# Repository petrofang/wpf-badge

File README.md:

# wpf-badge
A Printed Circuit Board design for When Pigs Fly, 
inspired by original artwork of Mark Poulin.

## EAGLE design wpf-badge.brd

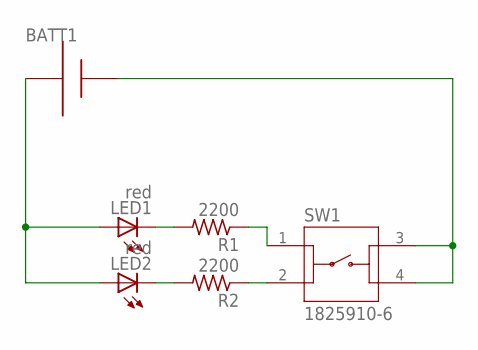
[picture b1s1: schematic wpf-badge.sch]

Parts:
BATT1: AAA; 12BH412
LED1, LED2: red; LED3MM
R1, R2: 2200; 0204/7
SW1: 1825910-6; SW_1825910-6-4

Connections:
unnamed: LED2.K (C), R2.2
unnamed: LED1.K (C), R1.2
unnamed: BATT1.+, SW1.3, SW1.4
unnamed: R1.1, SW1.1
unnamed: R2.1, SW1.2
unnamed: BATT1.-, LED1.A, LED2.A

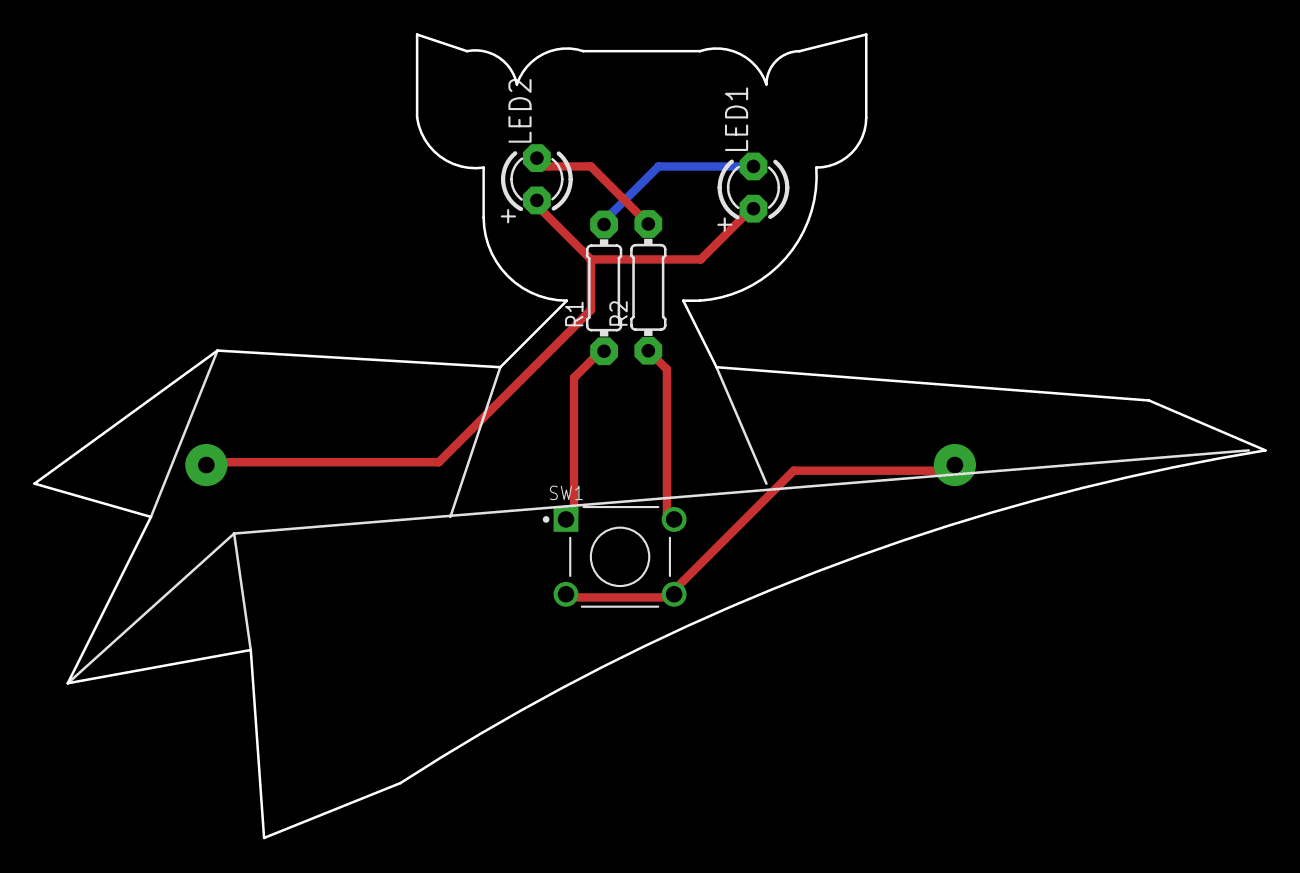
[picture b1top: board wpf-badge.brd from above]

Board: 2 copper layers, 74.0 x 48.3 mm, 6 parts (1 on the bottom side), 6 nets.

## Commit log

2019-02-24 Add files via upload
    A basic schematic and board outline inspired by original artwork by Mark Poulin.
2019-02-24 fiddled with the placement of button on board
2019-02-25 Tweak more board positioning. Minor update to schematic.
2019-02-25 Add rendor of board from EAGLE
2019-02-25 Add Bill of Materials (.csv) exported from EAGLE
